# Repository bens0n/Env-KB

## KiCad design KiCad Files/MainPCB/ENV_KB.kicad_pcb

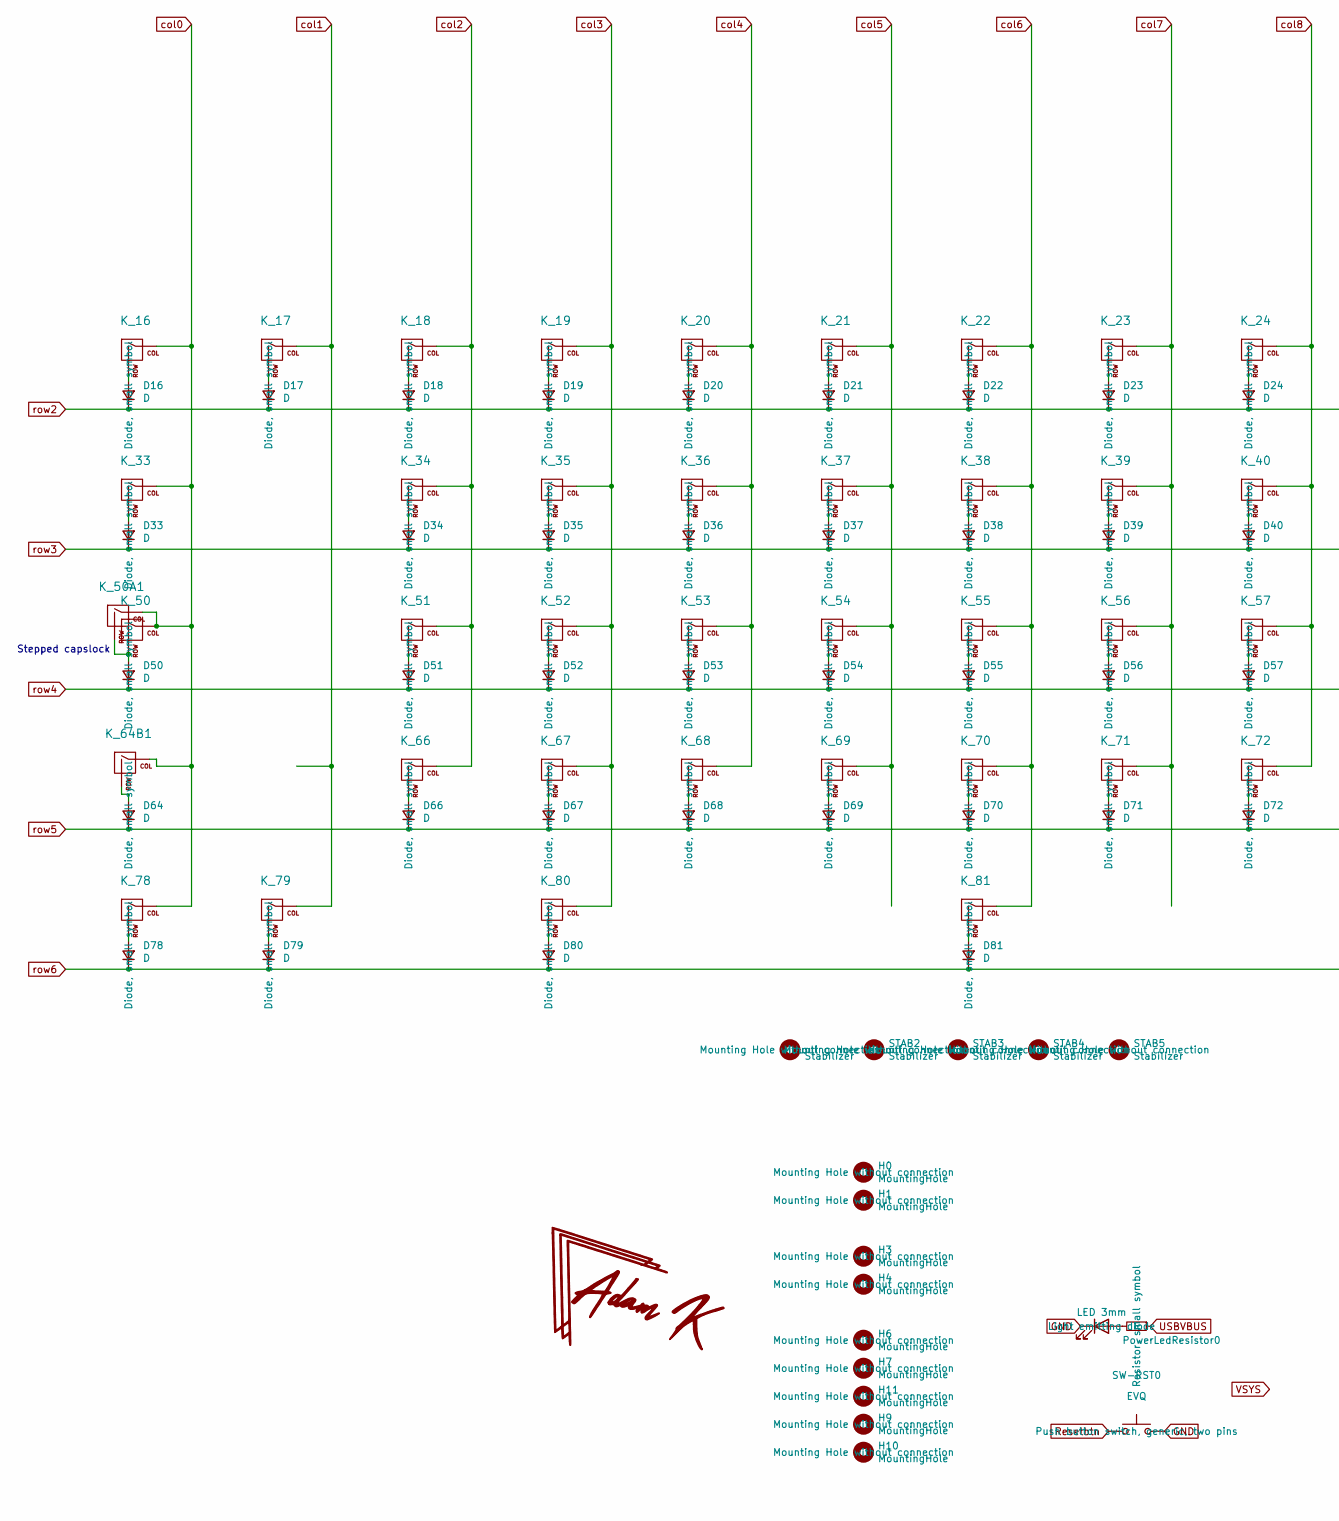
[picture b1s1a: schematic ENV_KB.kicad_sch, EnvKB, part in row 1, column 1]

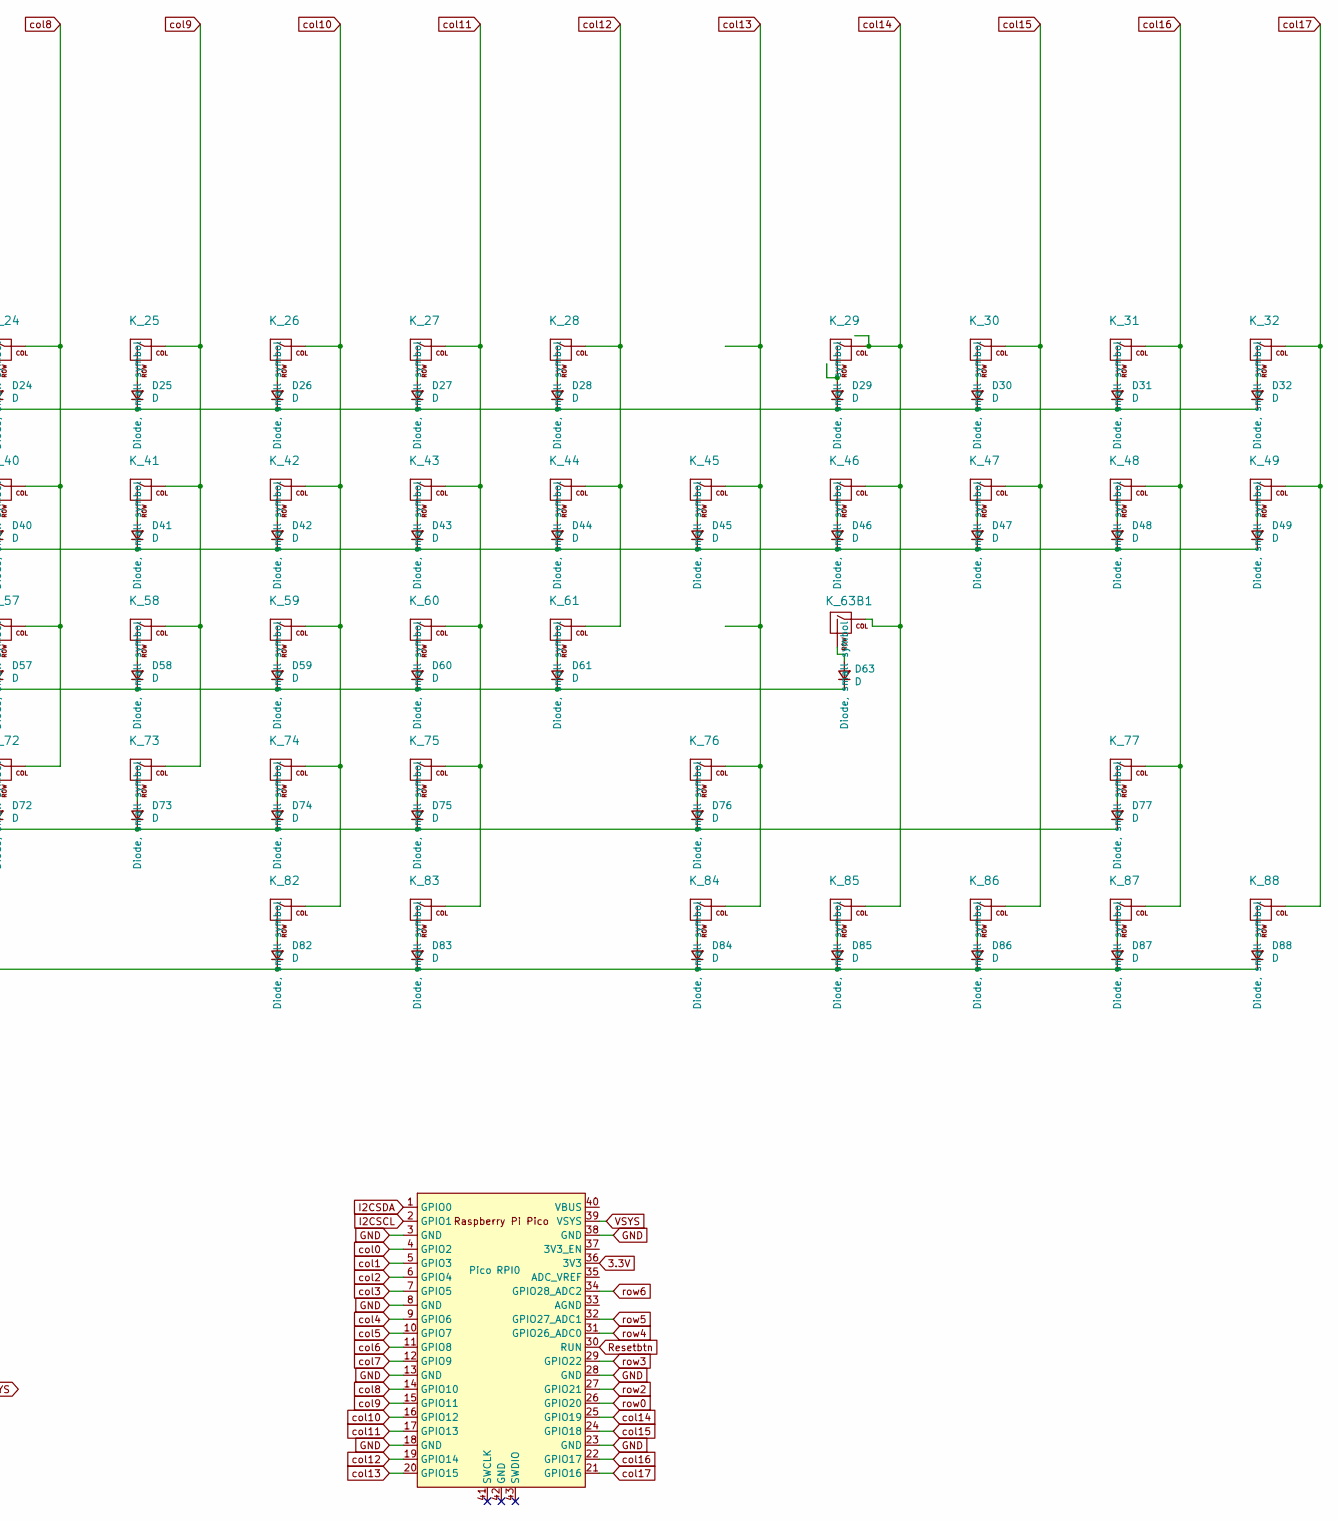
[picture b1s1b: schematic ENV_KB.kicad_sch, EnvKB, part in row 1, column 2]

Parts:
D16, D17, D18, D19, D20, D21, D22, D23, D24, D25, D26, D27, D28, D29, D30, D31, D32, D33, D34, D35, D36, D37, D38, D39, D40, D41, D42, D43, D44, D45, D46, D47, D48, D49, D50, D51, D52, D53, D54, D55, D56, D57, D58, D59, D60, D61, D63, D64, D66, D67, D68, D69, D70, D71, D72, D73, D74, D75, D76, D77, D78, D79, D80, D81, D82, D83, D84, D85, D86, D87, D88: D; D_DO-35_SOD27_P7.62mm_Horizontal
H0, H1, H3, H4, H6, H7, H9, H10, H11: MountingHole; MountingHole_2.2mm_M2_Pad
K_16, K_17, K_18, K_19, K_20, K_21, K_22, K_23, K_24, K_25, K_26, K_27, K_28, K_29, K_30, K_31, K_32, K_34, K_35, K_36, K_37, K_38, K_39, K_40, K_41, K_42, K_43, K_44, K_45, K_47, K_48, K_49, K_51, K_52, K_53, K_54, K_55, K_56, K_57, K_58, K_59, K_60, K_61, K_66, K_67, K_68, K_69, K_70, K_71, K_72, K_73, K_74, K_75, K_77, K_81, K_86, K_87, K_88: KEYSW; MXOnly-1U-NoLED
K_33, K_46: KEYSW; MXOnly-1.5U-NoLED
K_50: KEYSW; MXOnly-1.75U-NoLED
K_50A1, K_78, K_79, K_80, K_82, K_83, K_84, K_85: KEYSW; MXOnly-1.25U-NoLED
K_63B1: MX-NoLED; MXOnly-2.25U-NoLED
K_64B1: KEYSW; MXOnly-2.25U-NoLED
K_76: KEYSW; MXOnly-2.75U-NoLED
PowerLED0: LED 3mm; LED_D3.0mm
PowerLedResistor0: 47K Resistor; R_Axial_DIN0207_L6.3mm_D2.5mm_P7.62mm_Horizontal; LCSC C17513
RPI0: Pico; RPi_Pico_SMD_TH
STAB1, STAB2, STAB3, STAB4, STAB5: Stabilizer; Stabilizer_Cherry_MX_2u
SW-RST0: EVQ; Panasonic_EVQPUL_EVQPUC

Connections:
3.3V: RPI0.36 (3V3)
GND: PowerLED0.1 (K), RPI0.3 (GND), RPI0.8 (GND), RPI0.13 (GND), RPI0.18 (GND), RPI0.23 (GND), RPI0.28 (GND), RPI0.38 (GND), SW-RST0.2
I2CSCL: RPI0.2 (GPIO1)
I2CSDA: RPI0.1 (GPIO0)
unnamed: D16.2 (A), K_16.2 (ROW)
unnamed: D17.2 (A), K_17.2 (ROW)
unnamed: D18.2 (A), K_18.2 (ROW)
unnamed: D19.2 (A), K_19.2 (ROW)
unnamed: D20.2 (A), K_20.2 (ROW)
unnamed: D21.2 (A), K_21.2 (ROW)
unnamed: D22.2 (A), K_22.2 (ROW)
unnamed: D23.2 (A), K_23.2 (ROW)
unnamed: D24.2 (A), K_24.2 (ROW)
unnamed: D25.2 (A), K_25.2 (ROW)
unnamed: D26.2 (A), K_26.2 (ROW)
unnamed: D27.2 (A), K_27.2 (ROW)
unnamed: D28.2 (A), K_28.2 (ROW)
unnamed: D29.2 (A), K_29.2 (ROW)
unnamed: D30.2 (A), K_30.2 (ROW)
unnamed: D31.2 (A), K_31.2 (ROW)
unnamed: D32.2 (A), K_32.2 (ROW)
unnamed: D33.2 (A), K_33.2 (ROW)
unnamed: D34.2 (A), K_34.2 (ROW)
unnamed: D35.2 (A), K_35.2 (ROW)
unnamed: D36.2 (A), K_36.2 (ROW)
unnamed: D37.2 (A), K_37.2 (ROW)
unnamed: D38.2 (A), K_38.2 (ROW)
unnamed: D39.2 (A), K_39.2 (ROW)
unnamed: D40.2 (A), K_40.2 (ROW)
unnamed: D41.2 (A), K_41.2 (ROW)
unnamed: D42.2 (A), K_42.2 (ROW)
unnamed: D43.2 (A), K_43.2 (ROW)
unnamed: D44.2 (A), K_44.2 (ROW)
unnamed: D45.2 (A), K_45.2 (ROW)
unnamed: D46.2 (A), K_46.2 (ROW)
unnamed: D47.2 (A), K_47.2 (ROW)
unnamed: D48.2 (A), K_48.2 (ROW)
unnamed: D49.2 (A), K_49.2 (ROW)
unnamed: D50.2 (A), K_50.2 (ROW), K_50A1.2 (ROW)
unnamed: D51.2 (A), K_51.2 (ROW)
unnamed: D52.2 (A), K_52.2 (ROW)
unnamed: D53.2 (A), K_53.2 (ROW)
unnamed: D54.2 (A), K_54.2 (ROW)
unnamed: D55.2 (A), K_55.2 (ROW)
unnamed: D56.2 (A), K_56.2 (ROW)
unnamed: D57.2 (A), K_57.2 (ROW)
unnamed: D58.2 (A), K_58.2 (ROW)
unnamed: D59.2 (A), K_59.2 (ROW)
unnamed: D60.2 (A), K_60.2 (ROW)
unnamed: D61.2 (A), K_61.2 (ROW)
unnamed: D63.2 (A), K_63B1.2 (ROW)
unnamed: D64.2 (A), K_64B1.2 (ROW)
unnamed: D66.2 (A), K_66.2 (ROW)
unnamed: D67.2 (A), K_67.2 (ROW)
unnamed: D68.2 (A), K_68.2 (ROW)
unnamed: D69.2 (A), K_69.2 (ROW)
unnamed: D70.2 (A), K_70.2 (ROW)
unnamed: D71.2 (A), K_71.2 (ROW)
unnamed: D72.2 (A), K_72.2 (ROW)
unnamed: D73.2 (A), K_73.2 (ROW)
unnamed: D74.2 (A), K_74.2 (ROW)
unnamed: D75.2 (A), K_75.2 (ROW)
unnamed: D76.2 (A), K_76.2 (ROW)
unnamed: D77.2 (A), K_77.2 (ROW)
unnamed: D78.2 (A), K_78.2 (ROW)
unnamed: D79.2 (A), K_79.2 (ROW)
unnamed: D80.2 (A), K_80.2 (ROW)
unnamed: D81.2 (A), K_81.2 (ROW)
unnamed: D82.2 (A), K_82.2 (ROW)
unnamed: D83.2 (A), K_83.2 (ROW)
unnamed: D84.2 (A), K_84.2 (ROW)
unnamed: D85.2 (A), K_85.2 (ROW)
unnamed: D86.2 (A), K_86.2 (ROW)
unnamed: D87.2 (A), K_87.2 (ROW)
unnamed: D88.2 (A), K_88.2 (ROW)
unnamed: PowerLED0.2 (A), PowerLedResistor0.2
Resetbtn: RPI0.30 (RUN), SW-RST0.1
USBVBUS: PowerLedResistor0.1
VSYS: RPI0.39 (VSYS)
col0: K_16.1 (COL), K_33.1 (COL), K_50.1 (COL), K_50A1.1 (COL), K_64B1.1 (COL), K_78.1 (COL), RPI0.4 (GPIO2)
col1: K_17.1 (COL), K_79.1 (COL), RPI0.5 (GPIO3)
col2: K_18.1 (COL), K_34.1 (COL), K_51.1 (COL), K_66.1 (COL), RPI0.6 (GPIO4)
col3: K_19.1 (COL), K_35.1 (COL), K_52.1 (COL), K_67.1 (COL), K_80.1 (COL), RPI0.7 (GPIO5)
col4: K_20.1 (COL), K_36.1 (COL), K_53.1 (COL), K_68.1 (COL), RPI0.9 (GPIO6)
col5: K_21.1 (COL), K_37.1 (COL), K_54.1 (COL), K_69.1 (COL), RPI0.10 (GPIO7)
col6: K_22.1 (COL), K_38.1 (COL), K_55.1 (COL), K_70.1 (COL), K_81.1 (COL), RPI0.11 (GPIO8)
col7: K_23.1 (COL), K_39.1 (COL), K_56.1 (COL), K_71.1 (COL), RPI0.12 (GPIO9)
col8: K_24.1 (COL), K_40.1 (COL), K_57.1 (COL), K_72.1 (COL), RPI0.14 (GPIO10)
col9: K_25.1 (COL), K_41.1 (COL), K_58.1 (COL), K_73.1 (COL), RPI0.15 (GPIO11)
col10: K_26.1 (COL), K_42.1 (COL), K_59.1 (COL), K_74.1 (COL), K_82.1 (COL), RPI0.16 (GPIO12)
col11: K_27.1 (COL), K_43.1 (COL), K_60.1 (COL), K_75.1 (COL), K_83.1 (COL), RPI0.17 (GPIO13)
col12: K_28.1 (COL), K_44.1 (COL), K_61.1 (COL), RPI0.19 (GPIO14)
col13: K_45.1 (COL), K_76.1 (COL), K_84.1 (COL), RPI0.20 (GPIO15)
col14: K_29.1 (COL), K_46.1 (COL), K_63B1.1 (COL), K_85.1 (COL), RPI0.25 (GPIO19)
col15: K_30.1 (COL), K_47.1 (COL), K_86.1 (COL), RPI0.24 (GPIO18)
col16: K_31.1 (COL), K_48.1 (COL), K_77.1 (COL), K_87.1 (COL), RPI0.22 (GPIO17)
col17: K_32.1 (COL), K_49.1 (COL), K_88.1 (COL), RPI0.21 (GPIO16)
row0: RPI0.26 (GPIO20)
row2: D16.1 (K), D17.1 (K), D18.1 (K), D19.1 (K), D20.1 (K), D21.1 (K), D22.1 (K), D23.1 (K), D24.1 (K), D25.1 (K), D26.1 (K), D27.1 (K), D28.1 (K), D29.1 (K), D30.1 (K), D31.1 (K), D32.1 (K), RPI0.27 (GPIO21)
row3: D33.1 (K), D34.1 (K), D35.1 (K), D36.1 (K), D37.1 (K), D38.1 (K), D39.1 (K), D40.1 (K), D41.1 (K), D42.1 (K), D43.1 (K), D44.1 (K), D45.1 (K), D46.1 (K), D47.1 (K), D48.1 (K), D49.1 (K), RPI0.29 (GPIO22)
row4: D50.1 (K), D51.1 (K), D52.1 (K), D53.1 (K), D54.1 (K), D55.1 (K), D56.1 (K), D57.1 (K), D58.1 (K), D59.1 (K), D60.1 (K), D61.1 (K), D63.1 (K), RPI0.31 (GPIO26_ADC0)
row5: D64.1 (K), D66.1 (K), D67.1 (K), D68.1 (K), D69.1 (K), D70.1 (K), D71.1 (K), D72.1 (K), D73.1 (K), D74.1 (K), D75.1 (K), D76.1 (K), D77.1 (K), RPI0.32 (GPIO27_ADC1)
row6: D78.1 (K), D79.1 (K), D80.1 (K), D81.1 (K), D82.1 (K), D83.1 (K), D84.1 (K), D85.1 (K), D86.1 (K), D87.1 (K), D88.1 (K), RPI0.34 (GPIO28_ADC2)

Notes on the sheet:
Stepped capslock

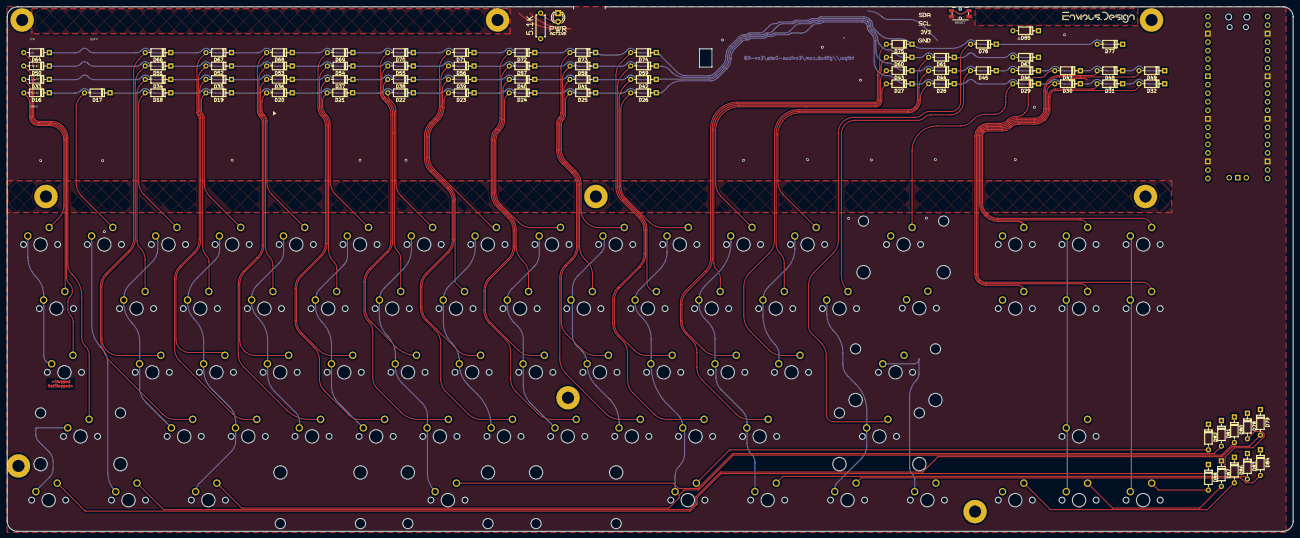
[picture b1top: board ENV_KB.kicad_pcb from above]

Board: 2 copper layers, 383.2 x 156.3 mm, 176 parts (1 on the bottom side), 97 nets.

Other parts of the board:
kibuzzard-628ADF99: G***; kibuzzard-628ADF99
kibuzzard-628AE7EF: G***; kibuzzard-628AE7EF
kibuzzard-628AE7FB: G***; kibuzzard-628AE7FB
kibuzzard-628AE8A6: G***; kibuzzard-628AE8A6
kibuzzard-628AE061: G***; kibuzzard-628AE061
kibuzzard-628AE80F: G***; kibuzzard-628AE80F
kibuzzard-628AE82F: G***; kibuzzard-628AE82F
kibuzzard-628AE768: G***; kibuzzard-628AE768
kibuzzard-628AE805: G***; kibuzzard-628AE805
kibuzzard-628AE860: G***; kibuzzard-628AE860
kibuzzard-628AE868: G***; kibuzzard-628AE868
kibuzzard-628AE874: G***; kibuzzard-628AE874
kibuzzard-628AE882: G***; kibuzzard-628AE882
kibuzzard-628AE933: G***; kibuzzard-628AE933
kibuzzard-628AE966: G***; kibuzzard-628AE966
kibuzzard-628AEA91: G***; kibuzzard-628AEA91
kibuzzard-6250C4E7: G***; kibuzzard-6250C4E7

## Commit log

2025-02-21 test reroute, row 1
2025-02-23 change controller; screw things up
2025-02-23 playing with layout
